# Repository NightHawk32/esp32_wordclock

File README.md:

# ESP32 WordClock - WiFi Setup Guide

This WordClock project is built around the **Ikea Sannahed 35x35cm picture frame**, transforming it into an elegant word-based time display with integrated sensors and web control.

## 📶 WiFi Setup

The WordClock features an automatic WiFi configuration system with two modes of operation:

### Initial Setup (Access Point Mode)

When the WordClock is powered on for the first time or cannot connect to a saved WiFi network, it automatically enters **Access Point (AP) Mode**:

1. **Connect to the WordClock's WiFi network:**
   - Network Name (SSID): `WordClock-Setup`
   - Password: `wordclock123`

2. **Access the configuration interface:**
   - Open your web browser and navigate to: `http://192.168.4.1`
   - You should see a yellow banner indicating "Access Point Mode"

3. **Configure your WiFi:**
   - Enter your home WiFi network name (SSID)
   - Enter your WiFi password
   - Click "Connect to WiFi"
   - The WordClock will save the settings and restart

4. **Reconnect to your home network:**
   - After restart, the WordClock will connect to your home WiFi
   - You can now disconnect from the `WordClock-Setup` network and reconnect to your home WiFi

### Normal Operation (Station Mode)

Once configured, the WordClock connects to your home WiFi network automatically. You can access the web interface in two ways:

#### Option 1: Using mDNS hostname (Recommended)
```
http://wordclock.local
```
This works on most devices without needing to know the IP address. The mDNS (Multicast DNS) service makes the WordClock discoverable on your local network.

> **Note:** mDNS may not work on all Android devices or older Windows versions. If `wordclock.local` doesn't work, use the IP address method below.

#### Option 2: Using IP Address
1. Check your router's DHCP client list to find the WordClock's IP address
2. Alternatively, connect via serial monitor (115200 baud) to see the IP address printed during startup
3. Navigate to: `http://[IP_ADDRESS]` (e.g., `http://192.168.1.100`)

## 🌐 Web Interface Features

Once connected, the web interface allows you to:

- **Display Mode:** Switch between word clock and digital clock modes
- **LED Color Control:** Adjust RGBW color values with preset options
- **Timezone Configuration:** Set your local timezone for accurate time display
- **Sensor Monitoring:** View real-time temperature, humidity, pressure, and brightness data
- **WiFi Reconfiguration:** Change WiFi settings if needed
- **Firmware Updates:** Update firmware over WiFi without USB cable (see OTA section below)

## 🔄 Over-The-Air (OTA) Firmware Updates

The WordClock supports wireless firmware updates, eliminating the need for USB cable after initial setup.

### Web-Based OTA Update (Recommended)

1. **Access the update page:**
   - Open http://wordclock.local
   - Click the "🔄 Go to Firmware Update Page" button
   - Or directly visit: http://wordclock.local/update

2. **Upload new firmware:**
   - Select the firmware file (`.bin`)
   - Click "Update"
   - Wait for the progress bar to complete
   - Device will automatically reboot

### PlatformIO Targets

You can also use PlatformIO to upload firmware over WiFi using the following target: OTA, which uses ArduinoOTA.
And uploads the firmware to the device over the network.
For the first upload you need to upload via the USB target to set up the WiFi connection.

### Windows Firewall / Defender Note

If OTA updates fail or timeout:
- **Windows Defender Firewall** may block OTA connections on port 3232
- **Solution:** Temporarily disable firewall or add exception for Python/PlatformIO
- **Alternative:** Use the web-based OTA method which uses standard HTTP port 80

## 🛠️ Hardware

This project is designed to fit perfectly in the **Ikea Sannahed 35x35cm picture frame**, providing a clean and modern aesthetic for your word clock display.

## 📝 Additional Configuration

After WiFi setup, you can configure:
- **Timezone:** Select from common timezones or use custom POSIX timezone strings
- **Display Colors:** Full RGBW control for customized appearance
- **Display Mode:** Choose between word-based or digital time display

The WordClock automatically syncs time via NTP (Network Time Protocol) when connected to WiFi, ensuring accurate timekeeping.

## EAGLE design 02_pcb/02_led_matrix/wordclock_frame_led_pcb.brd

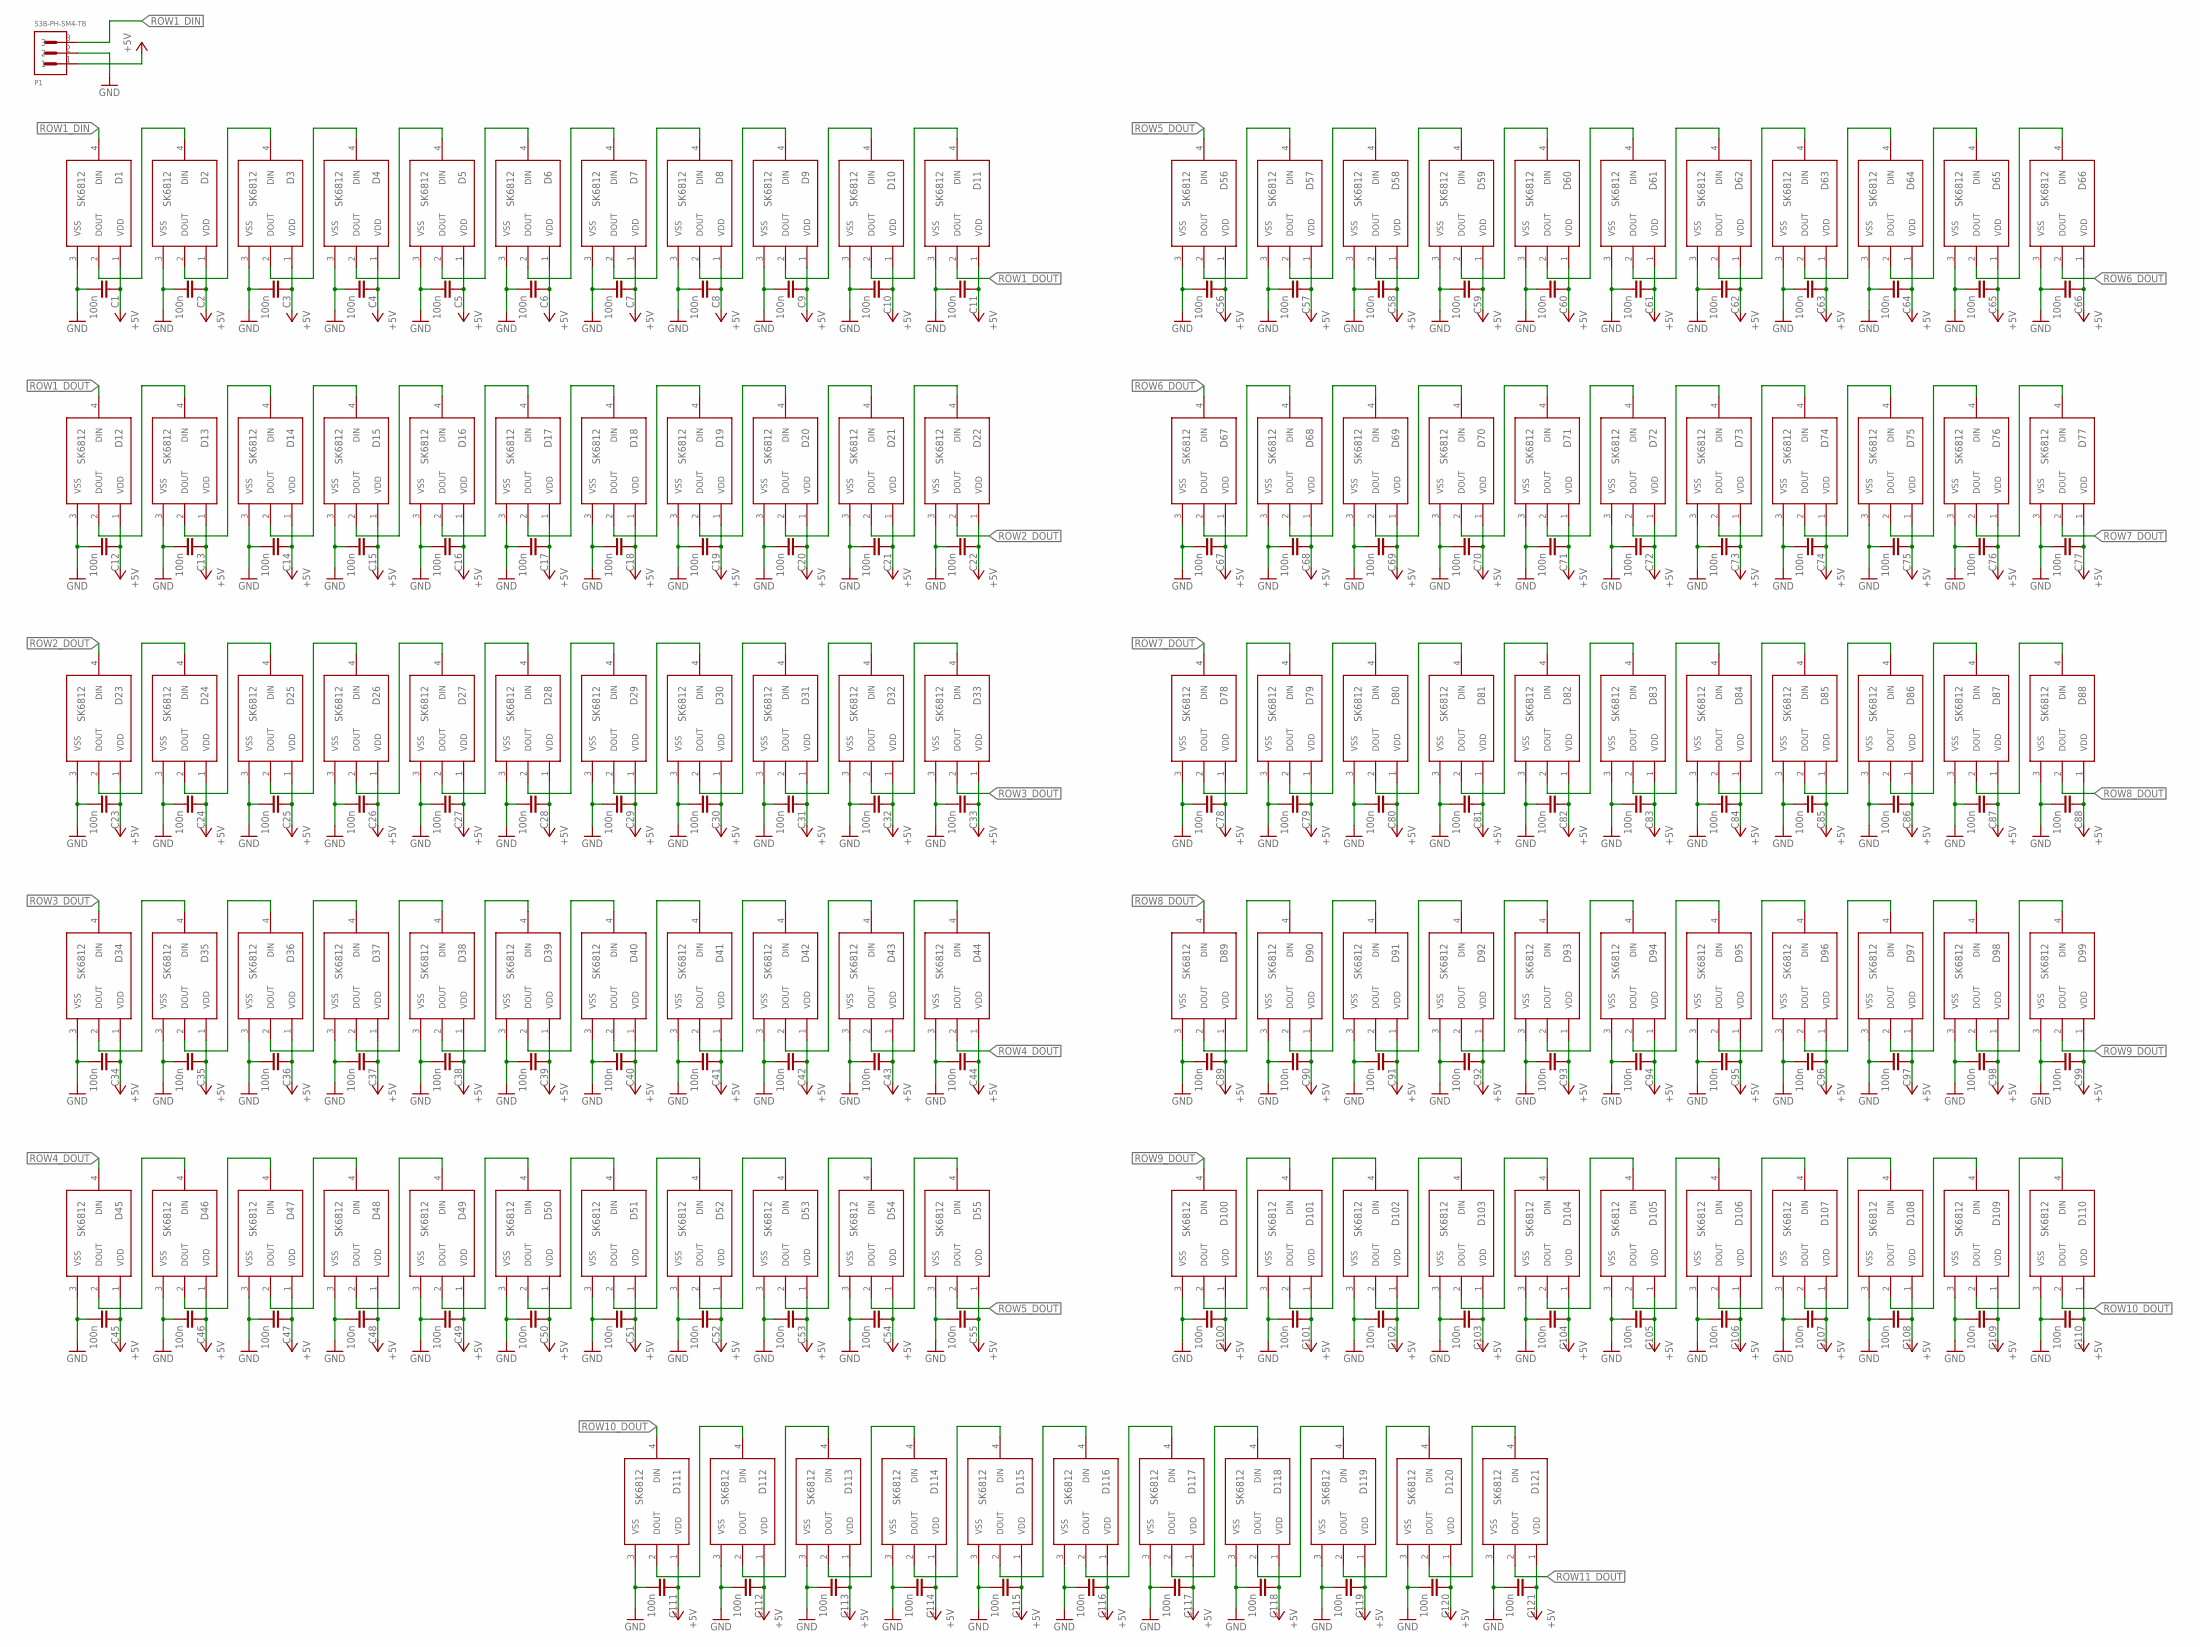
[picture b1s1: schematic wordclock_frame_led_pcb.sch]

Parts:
C1, C2, C3, C4, C5, C6, C7, C8, C9, C10, C11, C12, C13, C14, C15, C16, C17, C18, C19, C20, C21, C22, C23, C24, C25, C26, C27, C28, C29, C30, C31, C32, C33, C34, C35, C36, C37, C38, C39, C40, C41, C42, C43, C44, C45, C46, C47, C48, C49, C50, C51, C52, C53, C54, C55, C56, C57, C58, C59, C60, C61, C62, C63, C64, C65, C66, C67, C68, C69, C70, C71, C72, C73, C74, C75, C76, C77, C78, C79, C80, C81, C82, C83, C84, C85, C86, C87, C88, C89, C90, C91, C92, C93, C94, C95, C96, C97, C98, C99, C100, C101, C102, C103, C104, C105, C106, C107, C108, C109, C110, C111, C112, C113, C114, C115, C116, C117, C118, C119, C120, C121: 100n; C0603
D1, D2, D3, D4, D5, D6, D7, D8, D9, D10, D11, D12, D13, D14, D15, D16, D17, D18, D19, D20, D21, D22, D23, D24, D25, D26, D27, D28, D29, D30, D31, D32, D33, D34, D35, D36, D37, D38, D39, D40, D41, D42, D43, D44, D45, D46, D47, D48, D49, D50, D51, D52, D53, D54, D55, D56, D57, D58, D59, D60, D61, D62, D63, D64, D65, D66, D67, D68, D69, D70, D71, D72, D73, D74, D75, D76, D77, D78, D79, D80, D81, D82, D83, D84, D85, D86, D87, D88, D89, D90, D91, D92, D93, D94, D95, D96, D97, D98, D99, D100, D101, D102, D103, D104, D105, D106, D107, D108, D109, D110, D111, D112, D113, D114, D115, D116, D117, D118, D119, D120, D121: SK6812; LED_SK6812
P1: S3B-PH-SM4-TB; JST_S3B-PH-SM4-TB

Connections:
GND: C1.2, C2.2, C3.2, C4.2, C5.2, C6.2, C7.2, C8.2, C9.2, C10.2, C11.2, C12.2, C13.2, C14.2, C15.2, C16.2, C17.2, C18.2, C19.2, C20.2, C21.2, C22.2, C23.2, C24.2, C25.2, C26.2, C27.2, C28.2, C29.2, C30.2, C31.2, C32.2, C33.2, C34.2, C35.2, C36.2, C37.2, C38.2, C39.2, C40.2, C41.2, C42.2, C43.2, C44.2, C45.2, C46.2, C47.2, C48.2, C49.2, C50.2, C51.2, C52.2, C53.2, C54.2, C55.2, C56.2, C57.2, C58.2, C59.2, C60.2, C61.2, C62.2, C63.2, C64.2, C65.2, C66.2, C67.2, C68.2, C69.2, C70.2, C71.2, C72.2, C73.2, C74.2, C75.2, C76.2, C77.2, C78.2, C79.2, C80.2, C81.2, C82.2, C83.2, C84.2, C85.2, C86.2, C87.2, C88.2, C89.2, C90.2, C91.2, C92.2, C93.2, C94.2, C95.2, C96.2, C97.2, C98.2, C99.2, C100.2, C101.2, C102.2, C103.2, C104.2, C105.2, C106.2, C107.2, C108.2, C109.2, C110.2, C111.2, C112.2, C113.2, C114.2, C115.2, C116.2, C117.2, C118.2, C119.2, C120.2, C121.2, D1.3 (VSS), D2.3 (VSS), D3.3 (VSS), D4.3 (VSS), D5.3 (VSS), D6.3 (VSS), D7.3 (VSS), D8.3 (VSS), D9.3 (VSS), D10.3 (VSS), D11.3 (VSS), D12.3 (VSS), D13.3 (VSS), D14.3 (VSS), D15.3 (VSS), D16.3 (VSS), D17.3 (VSS), D18.3 (VSS), D19.3 (VSS), D20.3 (VSS), D21.3 (VSS), D22.3 (VSS), D23.3 (VSS), D24.3 (VSS), D25.3 (VSS), D26.3 (VSS), D27.3 (VSS), D28.3 (VSS), D29.3 (VSS), D30.3 (VSS), D31.3 (VSS), D32.3 (VSS), D33.3 (VSS), D34.3 (VSS), D35.3 (VSS), D36.3 (VSS), D37.3 (VSS), D38.3 (VSS), D39.3 (VSS), D40.3 (VSS), D41.3 (VSS), D42.3 (VSS), D43.3 (VSS), D44.3 (VSS), D45.3 (VSS), D46.3 (VSS), D47.3 (VSS), D48.3 (VSS), D49.3 (VSS), D50.3 (VSS), D51.3 (VSS), D52.3 (VSS), D53.3 (VSS), D54.3 (VSS), D55.3 (VSS), D56.3 (VSS), D57.3 (VSS), D58.3 (VSS), D59.3 (VSS), D60.3 (VSS), D61.3 (VSS), D62.3 (VSS), D63.3 (VSS), D64.3 (VSS), D65.3 (VSS), D66.3 (VSS), D67.3 (VSS), D68.3 (VSS), D69.3 (VSS), D70.3 (VSS), D71.3 (VSS), D72.3 (VSS), D73.3 (VSS), D74.3 (VSS), D75.3 (VSS), D76.3 (VSS), D77.3 (VSS), D78.3 (VSS), D79.3 (VSS), D80.3 (VSS), D81.3 (VSS), D82.3 (VSS), D83.3 (VSS), D84.3 (VSS), D85.3 (VSS), D86.3 (VSS), D87.3 (VSS), D88.3 (VSS), D89.3 (VSS), D90.3 (VSS), D91.3 (VSS), D92.3 (VSS), D93.3 (VSS), D94.3 (VSS), D95.3 (VSS), D96.3 (VSS), D97.3 (VSS), D98.3 (VSS), D99.3 (VSS), D100.3 (VSS), D101.3 (VSS), D102.3 (VSS), D103.3 (VSS), D104.3 (VSS), D105.3 (VSS), D106.3 (VSS), D107.3 (VSS), D108.3 (VSS), D109.3 (VSS), D110.3 (VSS), D111.3 (VSS), D112.3 (VSS), D113.3 (VSS), D114.3 (VSS), D115.3 (VSS), D116.3 (VSS), D117.3 (VSS), D118.3 (VSS), D119.3 (VSS), D120.3 (VSS), D121.3 (VSS), P1.2
unnamed: D1.2 (DOUT), D2.4 (DIN)
unnamed: D2.2 (DOUT), D3.4 (DIN)
unnamed: D3.2 (DOUT), D4.4 (DIN)
unnamed: D4.2 (DOUT), D5.4 (DIN)
unnamed: D5.2 (DOUT), D6.4 (DIN)
unnamed: D6.2 (DOUT), D7.4 (DIN)
unnamed: D7.2 (DOUT), D8.4 (DIN)
unnamed: D8.2 (DOUT), D9.4 (DIN)
unnamed: D9.2 (DOUT), D10.4 (DIN)
unnamed: D10.2 (DOUT), D11.4 (DIN)
unnamed: D12.2 (DOUT), D13.4 (DIN)
unnamed: D13.2 (DOUT), D14.4 (DIN)
unnamed: D14.2 (DOUT), D15.4 (DIN)
unnamed: D15.2 (DOUT), D16.4 (DIN)
unnamed: D16.2 (DOUT), D17.4 (DIN)
unnamed: D17.2 (DOUT), D18.4 (DIN)
unnamed: D18.2 (DOUT), D19.4 (DIN)
unnamed: D19.2 (DOUT), D20.4 (DIN)
unnamed: D20.2 (DOUT), D21.4 (DIN)
unnamed: D21.2 (DOUT), D22.4 (DIN)
unnamed: D23.2 (DOUT), D24.4 (DIN)
unnamed: D24.2 (DOUT), D25.4 (DIN)
unnamed: D25.2 (DOUT), D26.4 (DIN)
unnamed: D26.2 (DOUT), D27.4 (DIN)
unnamed: D27.2 (DOUT), D28.4 (DIN)
unnamed: D28.2 (DOUT), D29.4 (DIN)
unnamed: D29.2 (DOUT), D30.4 (DIN)
unnamed: D30.2 (DOUT), D31.4 (DIN)
unnamed: D31.2 (DOUT), D32.4 (DIN)
unnamed: D32.2 (DOUT), D33.4 (DIN)
unnamed: D34.2 (DOUT), D35.4 (DIN)
unnamed: D35.2 (DOUT), D36.4 (DIN)
unnamed: D36.2 (DOUT), D37.4 (DIN)
unnamed: D37.2 (DOUT), D38.4 (DIN)
unnamed: D38.2 (DOUT), D39.4 (DIN)
unnamed: D39.2 (DOUT), D40.4 (DIN)
unnamed: D40.2 (DOUT), D41.4 (DIN)
unnamed: D41.2 (DOUT), D42.4 (DIN)
unnamed: D42.2 (DOUT), D43.4 (DIN)
unnamed: D43.2 (DOUT), D44.4 (DIN)
unnamed: D45.2 (DOUT), D46.4 (DIN)
unnamed: D46.2 (DOUT), D47.4 (DIN)
unnamed: D47.2 (DOUT), D48.4 (DIN)
unnamed: D48.2 (DOUT), D49.4 (DIN)
unnamed: D49.2 (DOUT), D50.4 (DIN)
unnamed: D50.2 (DOUT), D51.4 (DIN)
unnamed: D51.2 (DOUT), D52.4 (DIN)
unnamed: D52.2 (DOUT), D53.4 (DIN)
unnamed: D53.2 (DOUT), D54.4 (DIN)
unnamed: D54.2 (DOUT), D55.4 (DIN)
unnamed: D56.2 (DOUT), D57.4 (DIN)
unnamed: D57.2 (DOUT), D58.4 (DIN)
unnamed: D58.2 (DOUT), D59.4 (DIN)
unnamed: D59.2 (DOUT), D60.4 (DIN)
unnamed: D60.2 (DOUT), D61.4 (DIN)
unnamed: D61.2 (DOUT), D62.4 (DIN)
unnamed: D62.2 (DOUT), D63.4 (DIN)
unnamed: D63.2 (DOUT), D64.4 (DIN)
unnamed: D64.2 (DOUT), D65.4 (DIN)
unnamed: D65.2 (DOUT), D66.4 (DIN)
unnamed: D67.2 (DOUT), D68.4 (DIN)
unnamed: D68.2 (DOUT), D69.4 (DIN)
unnamed: D69.2 (DOUT), D70.4 (DIN)
unnamed: D70.2 (DOUT), D71.4 (DIN)
unnamed: D71.2 (DOUT), D72.4 (DIN)
unnamed: D72.2 (DOUT), D73.4 (DIN)
unnamed: D73.2 (DOUT), D74.4 (DIN)
unnamed: D74.2 (DOUT), D75.4 (DIN)
unnamed: D75.2 (DOUT), D76.4 (DIN)
unnamed: D76.2 (DOUT), D77.4 (DIN)
unnamed: D78.2 (DOUT), D79.4 (DIN)
unnamed: D79.2 (DOUT), D80.4 (DIN)
unnamed: D80.2 (DOUT), D81.4 (DIN)
unnamed: D81.2 (DOUT), D82.4 (DIN)
unnamed: D82.2 (DOUT), D83.4 (DIN)
unnamed: D83.2 (DOUT), D84.4 (DIN)
unnamed: D84.2 (DOUT), D85.4 (DIN)
unnamed: D85.2 (DOUT), D86.4 (DIN)
unnamed: D86.2 (DOUT), D87.4 (DIN)
unnamed: D87.2 (DOUT), D88.4 (DIN)
unnamed: D89.2 (DOUT), D90.4 (DIN)
unnamed: D90.2 (DOUT), D91.4 (DIN)
unnamed: D91.2 (DOUT), D92.4 (DIN)
unnamed: D92.2 (DOUT), D93.4 (DIN)
unnamed: D93.2 (DOUT), D94.4 (DIN)
unnamed: D94.2 (DOUT), D95.4 (DIN)
unnamed: D95.2 (DOUT), D96.4 (DIN)
unnamed: D96.2 (DOUT), D97.4 (DIN)
unnamed: D97.2 (DOUT), D98.4 (DIN)
unnamed: D98.2 (DOUT), D99.4 (DIN)
unnamed: D100.2 (DOUT), D101.4 (DIN)
unnamed: D101.2 (DOUT), D102.4 (DIN)
unnamed: D102.2 (DOUT), D103.4 (DIN)
unnamed: D103.2 (DOUT), D104.4 (DIN)
unnamed: D104.2 (DOUT), D105.4 (DIN)
unnamed: D105.2 (DOUT), D106.4 (DIN)
unnamed: D106.2 (DOUT), D107.4 (DIN)
unnamed: D107.2 (DOUT), D108.4 (DIN)
unnamed: D108.2 (DOUT), D109.4 (DIN)
unnamed: D109.2 (DOUT), D110.4 (DIN)
unnamed: D111.2 (DOUT), D112.4 (DIN)
unnamed: D112.2 (DOUT), D113.4 (DIN)
unnamed: D113.2 (DOUT), D114.4 (DIN)
unnamed: D114.2 (DOUT), D115.4 (DIN)
unnamed: D115.2 (DOUT), D116.4 (DIN)
unnamed: D116.2 (DOUT), D117.4 (DIN)
unnamed: D117.2 (DOUT), D118.4 (DIN)
unnamed: D118.2 (DOUT), D119.4 (DIN)
unnamed: D119.2 (DOUT), D120.4 (DIN)
unnamed: D120.2 (DOUT), D121.4 (DIN)
ROW1_DIN: D1.4 (DIN), P1.3
ROW1_DOUT: D11.2 (DOUT), D12.4 (DIN)
ROW2_DOUT: D22.2 (DOUT), D23.4 (DIN)
ROW3_DOUT: D33.2 (DOUT), D34.4 (DIN)
ROW4_DOUT: D44.2 (DOUT), D45.4 (DIN)
ROW5_DOUT: D55.2 (DOUT), D56.4 (DIN)
ROW6_DOUT: D66.2 (DOUT), D67.4 (DIN)
ROW7_DOUT: D77.2 (DOUT), D78.4 (DIN)
ROW8_DOUT: D88.2 (DOUT), D89.4 (DIN)
ROW9_DOUT: D99.2 (DOUT), D100.4 (DIN)
ROW10_DOUT: D110.2 (DOUT), D111.4 (DIN)
ROW11_DOUT: D121.2 (DOUT)
VCC: C1.1, C2.1, C3.1, C4.1, C5.1, C6.1, C7.1, C8.1, C9.1, C10.1, C11.1, C12.1, C13.1, C14.1, C15.1, C16.1, C17.1, C18.1, C19.1, C20.1, C21.1, C22.1, C23.1, C24.1, C25.1, C26.1, C27.1, C28.1, C29.1, C30.1, C31.1, C32.1, C33.1, C34.1, C35.1, C36.1, C37.1, C38.1, C39.1, C40.1, C41.1, C42.1, C43.1, C44.1, C45.1, C46.1, C47.1, C48.1, C49.1, C50.1, C51.1, C52.1, C53.1, C54.1, C55.1, C56.1, C57.1, C58.1, C59.1, C60.1, C61.1, C62.1, C63.1, C64.1, C65.1, C66.1, C67.1, C68.1, C69.1, C70.1, C71.1, C72.1, C73.1, C74.1, C75.1, C76.1, C77.1, C78.1, C79.1, C80.1, C81.1, C82.1, C83.1, C84.1, C85.1, C86.1, C87.1, C88.1, C89.1, C90.1, C91.1, C92.1, C93.1, C94.1, C95.1, C96.1, C97.1, C98.1, C99.1, C100.1, C101.1, C102.1, C103.1, C104.1, C105.1, C106.1, C107.1, C108.1, C109.1, C110.1, C111.1, C112.1, C113.1, C114.1, C115.1, C116.1, C117.1, C118.1, C119.1, C120.1, C121.1, D1.1 (VDD), D2.1 (VDD), D3.1 (VDD), D4.1 (VDD), D5.1 (VDD), D6.1 (VDD), D7.1 (VDD), D8.1 (VDD), D9.1 (VDD), D10.1 (VDD), D11.1 (VDD), D12.1 (VDD), D13.1 (VDD), D14.1 (VDD), D15.1 (VDD), D16.1 (VDD), D17.1 (VDD), D18.1 (VDD), D19.1 (VDD), D20.1 (VDD), D21.1 (VDD), D22.1 (VDD), D23.1 (VDD), D24.1 (VDD), D25.1 (VDD), D26.1 (VDD), D27.1 (VDD), D28.1 (VDD), D29.1 (VDD), D30.1 (VDD), D31.1 (VDD), D32.1 (VDD), D33.1 (VDD), D34.1 (VDD), D35.1 (VDD), D36.1 (VDD), D37.1 (VDD), D38.1 (VDD), D39.1 (VDD), D40.1 (VDD), D41.1 (VDD), D42.1 (VDD), D43.1 (VDD), D44.1 (VDD), D45.1 (VDD), D46.1 (VDD), D47.1 (VDD), D48.1 (VDD), D49.1 (VDD), D50.1 (VDD), D51.1 (VDD), D52.1 (VDD), D53.1 (VDD), D54.1 (VDD), D55.1 (VDD), D56.1 (VDD), D57.1 (VDD), D58.1 (VDD), D59.1 (VDD), D60.1 (VDD), D61.1 (VDD), D62.1 (VDD), D63.1 (VDD), D64.1 (VDD), D65.1 (VDD), D66.1 (VDD), D67.1 (VDD), D68.1 (VDD), D69.1 (VDD), D70.1 (VDD), D71.1 (VDD), D72.1 (VDD), D73.1 (VDD), D74.1 (VDD), D75.1 (VDD), D76.1 (VDD), D77.1 (VDD), D78.1 (VDD), D79.1 (VDD), D80.1 (VDD), D81.1 (VDD), D82.1 (VDD), D83.1 (VDD), D84.1 (VDD), D85.1 (VDD), D86.1 (VDD), D87.1 (VDD), D88.1 (VDD), D89.1 (VDD), D90.1 (VDD), D91.1 (VDD), D92.1 (VDD), D93.1 (VDD), D94.1 (VDD), D95.1 (VDD), D96.1 (VDD), D97.1 (VDD), D98.1 (VDD), D99.1 (VDD), D100.1 (VDD), D101.1 (VDD), D102.1 (VDD), D103.1 (VDD), D104.1 (VDD), D105.1 (VDD), D106.1 (VDD), D107.1 (VDD), D108.1 (VDD), D109.1 (VDD), D110.1 (VDD), D111.1 (VDD), D112.1 (VDD), D113.1 (VDD), D114.1 (VDD), D115.1 (VDD), D116.1 (VDD), D117.1 (VDD), D118.1 (VDD), D119.1 (VDD), D120.1 (VDD), D121.1 (VDD), P1.1

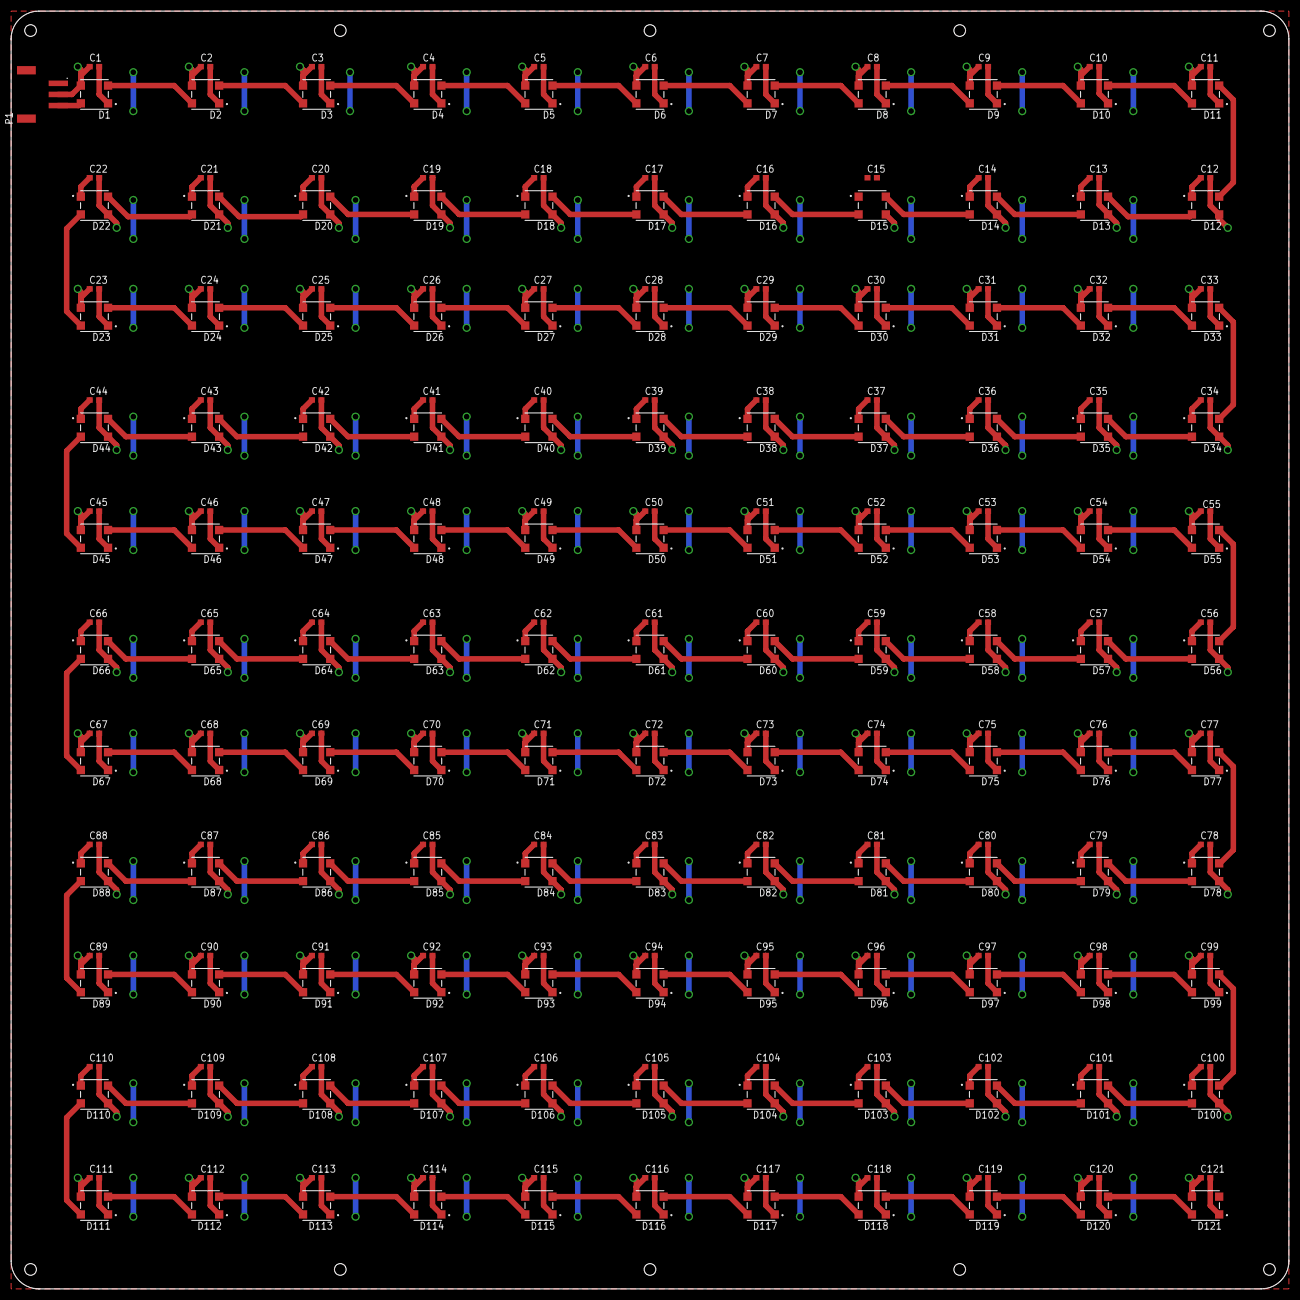
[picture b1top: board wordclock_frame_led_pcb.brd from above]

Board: 2 copper layers, 230.0 x 230.0 mm, 243 parts (0 on the bottom side), 123 nets.

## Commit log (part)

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2024-04-17 added matrix test code2
2024-04-18 added digital mode
2024-04-26 some code cleanup, added support for TSL2561
2026-01-20 added more resources and fixed small bug
2026-01-20 added CAD data and BME688 driver
2026-01-20 added webpage for config
2026-01-21 added web OTA
2026-01-23 fixed bug when showing "eins"
